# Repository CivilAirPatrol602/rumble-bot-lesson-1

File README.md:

# Rumble-Bot Lesson 1

Lesson 1 focuses on soldering the Rumble-Bot power board and designing the
Rumble-Bot microcontroller board by adding copper traces.

## Directory Contents

* [01-power](01-power/README.md): The completed Ardustack power board; cadets
  assemble and solder a power board as part of Lesson 1
* [02-processor](02-processor/README.md): The Ardustack microcontroller board;
  cadets route the board traces as part of Lesson 1
* [LICENSE](LICENSE): License for the non-hardware portions of the repository
* [README.md](README.md): This document

## License

Written by Bradley Denby  
Other contributors: None

See the [LICENSE](LICENSE) file for license details.

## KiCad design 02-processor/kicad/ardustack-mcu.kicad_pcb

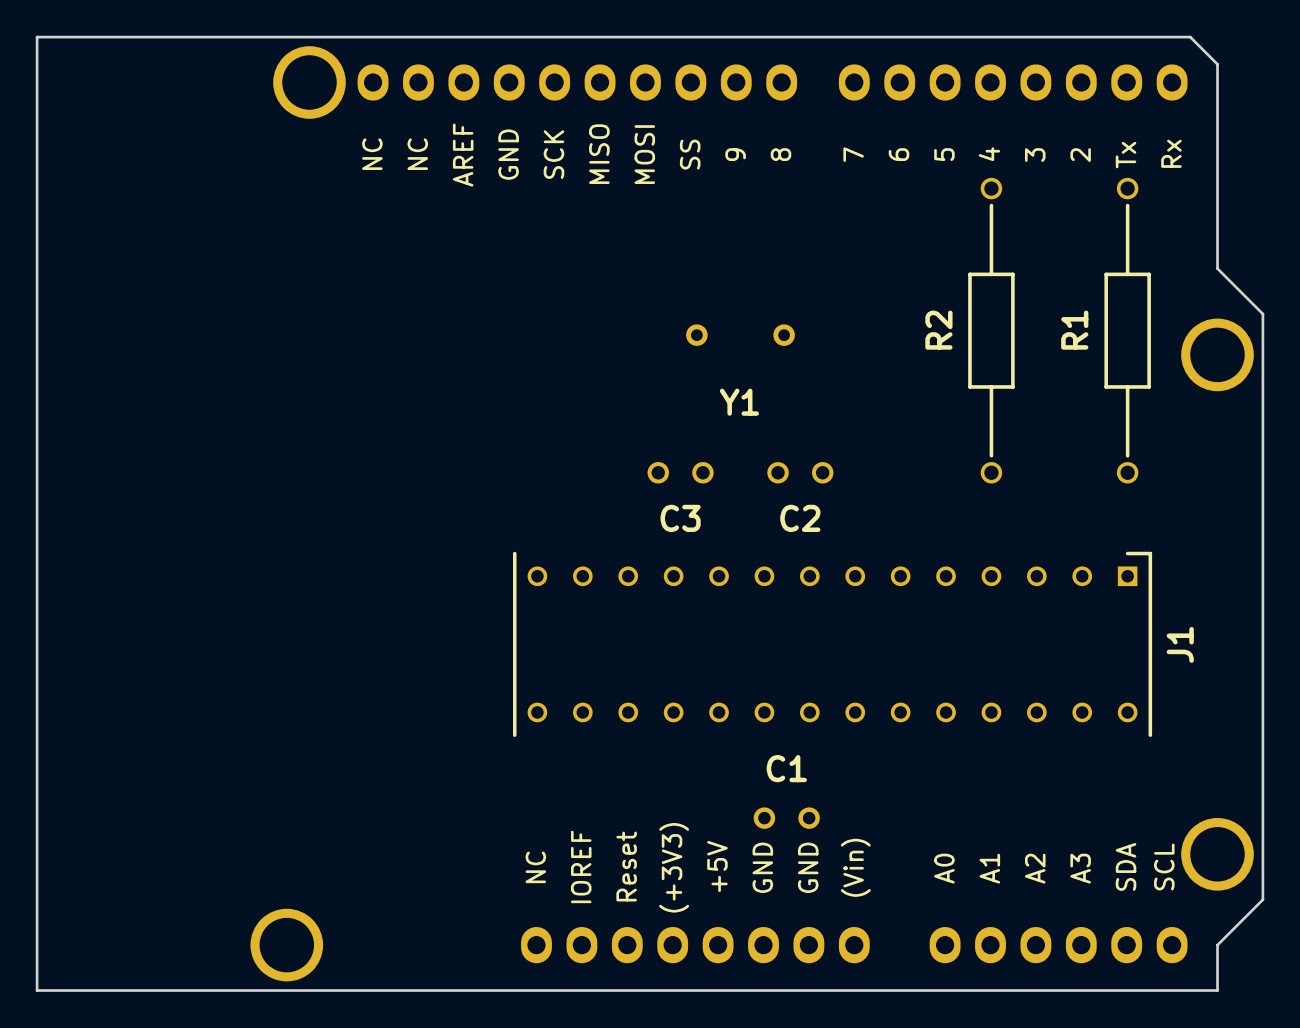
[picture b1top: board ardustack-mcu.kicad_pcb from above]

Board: 2 copper layers, 68.6 x 53.3 mm, 15 parts (0 on the bottom side), 28 nets, no tracks yet.

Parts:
C1: K105Z20Y5VF5TL2
C2, C3: K220J15C0GF5TL2
J1: 1-2199298-9; DIPS1524W51P254L3556H457Q28N
P1: Power; Socket_Strip_Arduino_1x08
P2: Analog; Socket_Strip_Arduino_1x06
P3: Digital; Socket_Strip_Arduino_1x10
P4: Digital; Socket_Strip_Arduino_1x08
P5, P6, P7, P8: CONN_01X01; Arduino_1pin
R1, R2: CFR-25JR-52-10K; RESAD1590W60L630D240
Y1: ABL-16.000MHZ-B2; ABL16000MHZB2

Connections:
+5V: C1.1, J1.7, J1.20, P1.2, P1.5
/0(Rx): P4.8, R1.2
/1(Tx): P4.7, R2.2
/2: J1.4, P4.6
/3(**): J1.5, P4.5
/4: J1.6, P4.4
/5(**): J1.11, P4.3
/6(**): J1.12, P4.2
/7: J1.13, P4.1
/8: J1.14, P3.10
/9(**): J1.15, P3.9
/10(**/SS): J1.16, P3.8
/11(**/MOSI): J1.17, P3.7
/12(MISO): J1.18, P3.6
/13(SCK): J1.19, P3.5
/A0: J1.23, P2.1
/A1: J1.24, P2.2
/A2: J1.25, P2.3
/A3: J1.26, P2.4
/A4(SDA): J1.27, P2.5
/A5(SCL): J1.28, P2.6
/AREF: J1.21, P3.3
/CLK1: C2.1, J1.9, Y1.1 (X1)
/CLK2: C3.1, J1.10, Y1.2 (X2)
/Reset: J1.1, P1.3
GND: C1.2, C2.2, C3.2, J1.8, J1.22, P1.6, P1.7, P3.4
unnamed: J1.2, R1.1
unnamed: J1.3, R2.1

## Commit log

2022-02-18 Rumble-Bot Lesson 1
2022-02-28 Adds documentation files
